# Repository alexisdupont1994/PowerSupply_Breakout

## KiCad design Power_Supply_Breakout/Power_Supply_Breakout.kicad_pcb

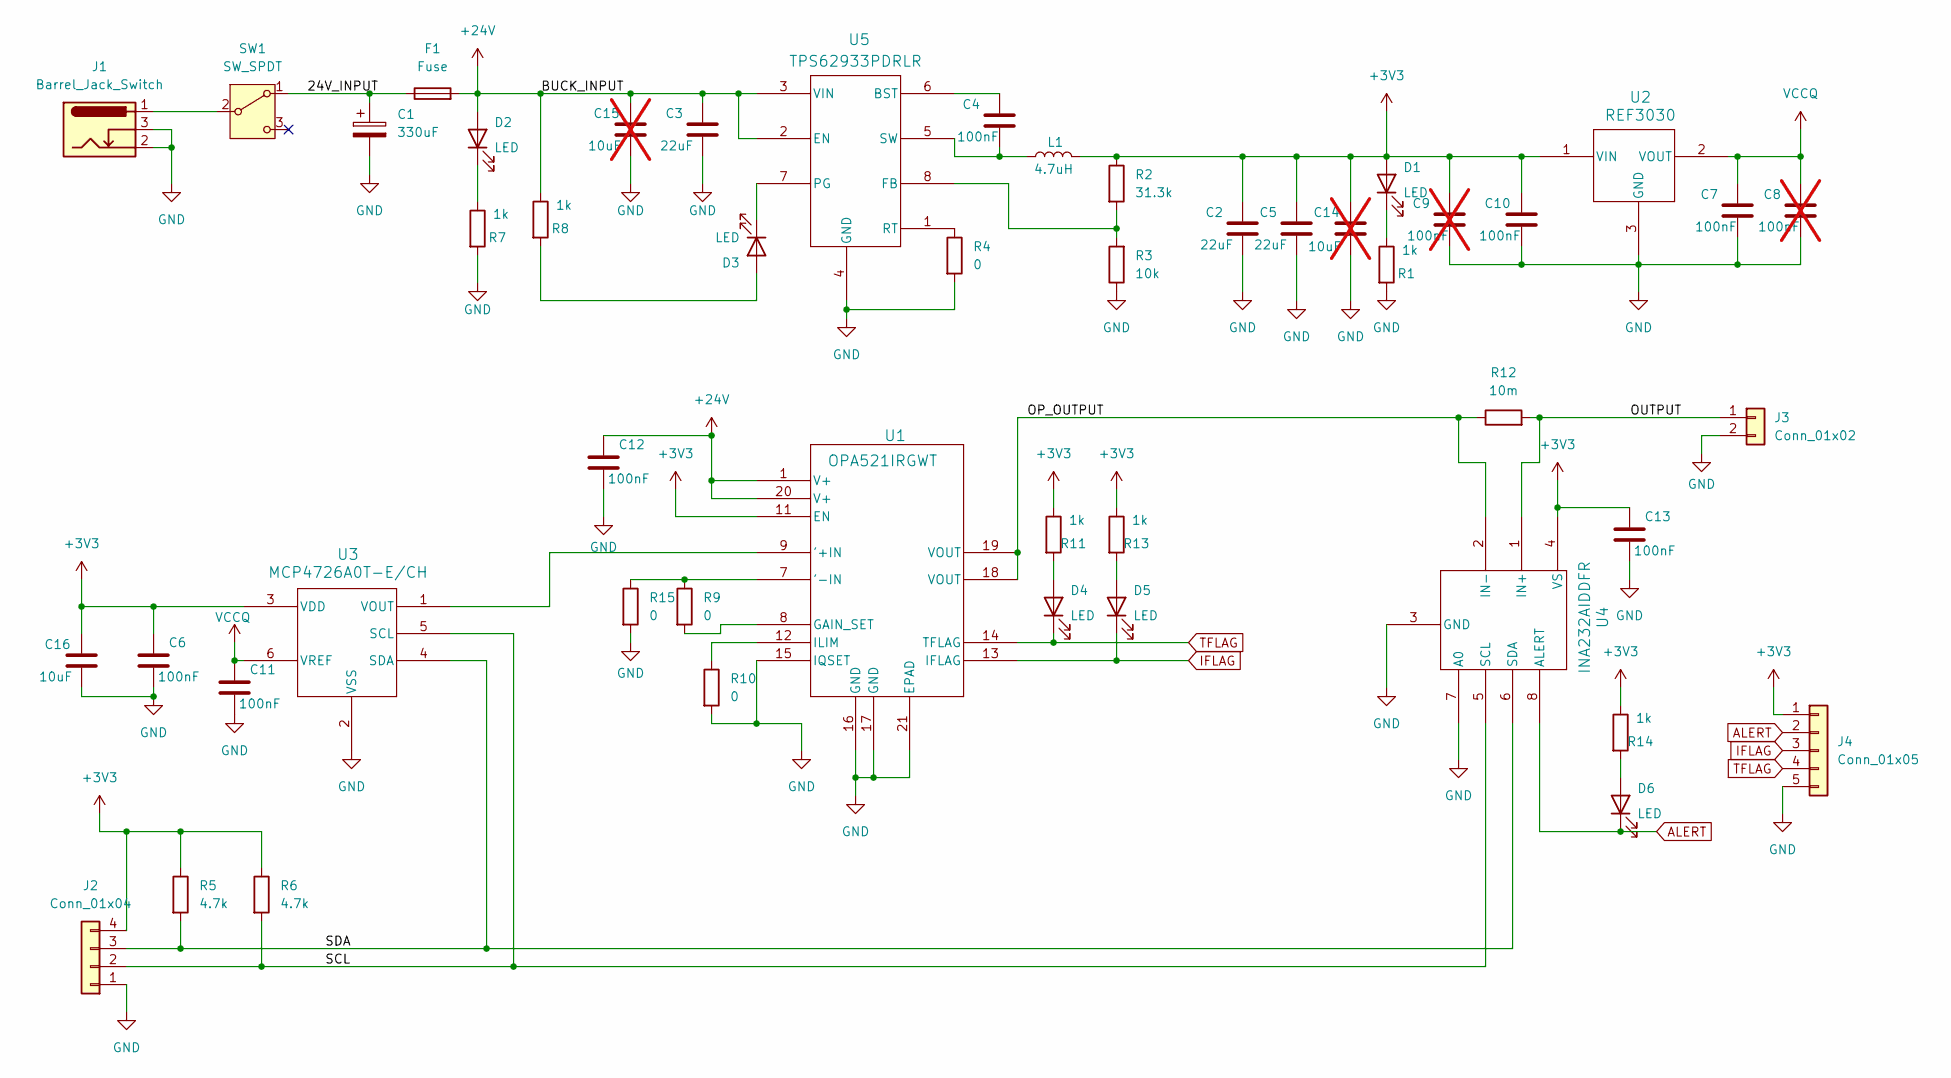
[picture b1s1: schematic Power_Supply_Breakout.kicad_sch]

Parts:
C1: 330uF; ECA-1HM331B
C2, C3, C5: 22uF; C_0805_2012Metric_Pad1.18x1.45mm_HandSolder
C4, C6, C7, C10, C11, C12, C13: 100nF; C_0805_2012Metric_Pad1.18x1.45mm_HandSolder
C8, C9: 100nF; C_0805_2012Metric_Pad1.18x1.45mm_HandSolder; not fitted
C14, C15: 10uF; C_1206_3216Metric_Pad1.33x1.80mm_HandSolder; not fitted
C16: 10uF; C_1206_3216Metric_Pad1.33x1.80mm_HandSolder
D1, D2, D3, D4, D5, D6: LED; LED_0805_2012Metric
F1: Fuse; Fuse_1206_3216Metric_Pad1.42x1.75mm_HandSolder
J1: Barrel_Jack_Switch; CUI_PJ-059A
J2: Conn_01x04; PinHeader_1x04_P2.54mm_Vertical
J3: Conn_01x02; PHOENIX_1725656
J4: Conn_01x05; PinHeader_1x05_P2.54mm_Vertical
L1: 4.7uH; IND_1255AY-4R7M=P3
R1, R7, R8, R11, R13, R14: 1k; R_0805_2012Metric_Pad1.20x1.40mm_HandSolder
R2: 31.3k; R_0805_2012Metric_Pad1.20x1.40mm_HandSolder
R3: 10k; R_0805_2012Metric_Pad1.20x1.40mm_HandSolder
R4, R9, R10, R15: 0; R_0805_2012Metric_Pad1.20x1.40mm_HandSolder
R5, R6: 4.7k; R_0805_2012Metric_Pad1.20x1.40mm_HandSolder
R12: 10m; R_0805_2012Metric_Pad1.20x1.40mm_HandSolder
SW1: SW_SPDT; L102021MS02Q
U1: OPA521IRGWT; OPA521IRGWT-M
U2: REF3030; REF3030-M
U3: MCP4726A0T-E/CH; MCP4726A0T_E_CH-M
U4: INA232AIDDFR; INA232AIDDFR-M
U5: TPS62933PDRLR; TPS62933PDRLR-M

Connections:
+3V3: C2.1, C5.1, C6.1, C9.1, C10.1, C13.1, C14.1, C16.1, D1.2 (A), J2.4, J4.1, L1.2, R2.1, R5.1, R6.1, R11.1, R13.1, R14.1, U1.11 (EN), U2.1 (VIN), U3.3 (VDD), U4.4 (VS)
+24V: C3.1, C12.1, C15.1, D2.2 (A), F1.2, R8.1, U1.1 (V+), U1.20 (V+), U5.2 (EN), U5.3 (VIN)
/24V_INPUT: C1.1, F1.1, SW1.1 (A)
/OP_OUTPUT: R12.1, U1.18 (VOUT), U1.19 (VOUT), U4.2 (IN-)
/OUTPUT: J3.1, R12.2, U4.1 (IN+)
/SCL: J2.2, R6.2, U3.5 (SCL), U4.5 (SCL)
/SDA: J2.3, R5.2, U3.4 (SDA), U4.6 (SDA)
ALERT: D6.1 (K), J4.2, U4.8 (ALERT)
GND: C1.2, C2.2, C3.2, C5.2, C6.2, C7.2, C8.2, C9.2, C10.2, C11.2, C12.2, C13.2, C14.2, C15.2, C16.2, J1.2, J1.3, J2.1, J3.2, J4.5, R1.2, R3.1, R4.2, R7.2, R10.2, R15.2, U1.15 (IQSET), U1.16 (GND), U1.17 (GND), U1.21 (EPAD), U2.3 (GND), U3.2 (VSS), U4.3 (GND), U4.7 (A0), U5.4 (GND)
IFLAG: D5.1 (K), J4.3, U1.13 (IFLAG)
unnamed: D1.1 (K), R1.1
unnamed: D2.1 (K), R7.1
unnamed: D3.2 (A), R8.2
unnamed: D3.1 (K), U5.7 (PG)
unnamed: D4.2 (A), R11.2
unnamed: D5.2 (A), R13.2
unnamed: D6.2 (A), R14.2
unnamed: J1.1, SW1.2 (B)
unnamed: U1.9 ('+IN), U3.1 (VOUT)
unnamed: R9.1, R15.1, U1.7 ('-IN)
unnamed: R9.2, U1.8 (GAIN_SET)
unnamed: R10.1, U1.12 (ILIM)
unnamed: C4.1, U5.6 (BST)
unnamed: R2.2, R3.2, U5.8 (FB)
unnamed: R4.1, U5.1 (RT)
unnamed: C4.2, L1.1, U5.5 (SW)
TFLAG: D4.1 (K), J4.4, U1.14 (TFLAG)
VCCQ: C7.1, C8.1, C11.1, U2.2 (VOUT), U3.6 (VREF)

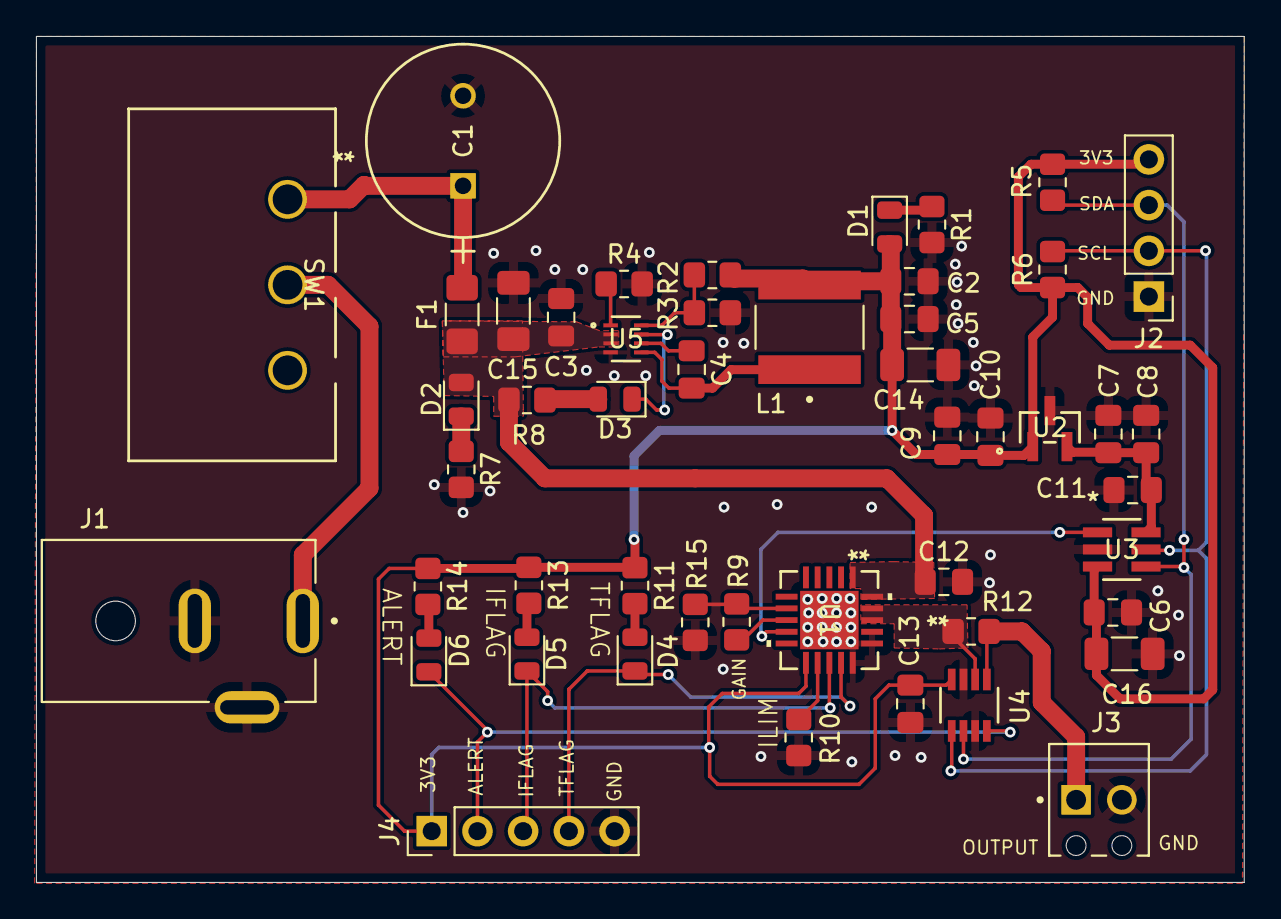
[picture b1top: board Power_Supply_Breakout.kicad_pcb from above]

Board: 4 copper layers, 67.1 x 47.0 mm, 49 parts (0 on the bottom side), 28 nets.

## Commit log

2024-08-04 2024-08-03 : Everything work, but the opamp get too hot. The PCB will be changed to have the OPAXXX to handle the power. In development
